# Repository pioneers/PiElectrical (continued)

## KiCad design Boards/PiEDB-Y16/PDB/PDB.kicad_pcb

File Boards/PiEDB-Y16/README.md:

# Power Distribution Board
## Pioneers in Engineering Year 2023-2024
---
Continuation of Y15's PDB.
  
**To Do:**  
- Add battery calibration **(Added switch, WIP for runtime)**
- Create DC-DC Converter **(Work In Progress)**
- Fix battery shorting problem **(Complete)**
- Remove power from data port, optional power using shortings **(Complete)**
- Consider using different port for 5v **(Kept as USB)**

**To Do: Large Revision**
- Find a switch rated for 50A @ 12VDC
- Fuse each motor controller port with 7.5A slow-blow fuse (MC rated for 2x 3.5A motors) (Blows in 20Sec at 10A)
- Add 40A slow-blow fuse for battery. (Blows in 5 min @ 50A, Blows in 20 sec @ 55A) (Battery Max is 55A)
- Add 7.5A slow-blow fuse for 5V rail. (Follows 7.5A max in dc-dc converter)
- Add additional USB plug    
- Rework traces/power planes for large current

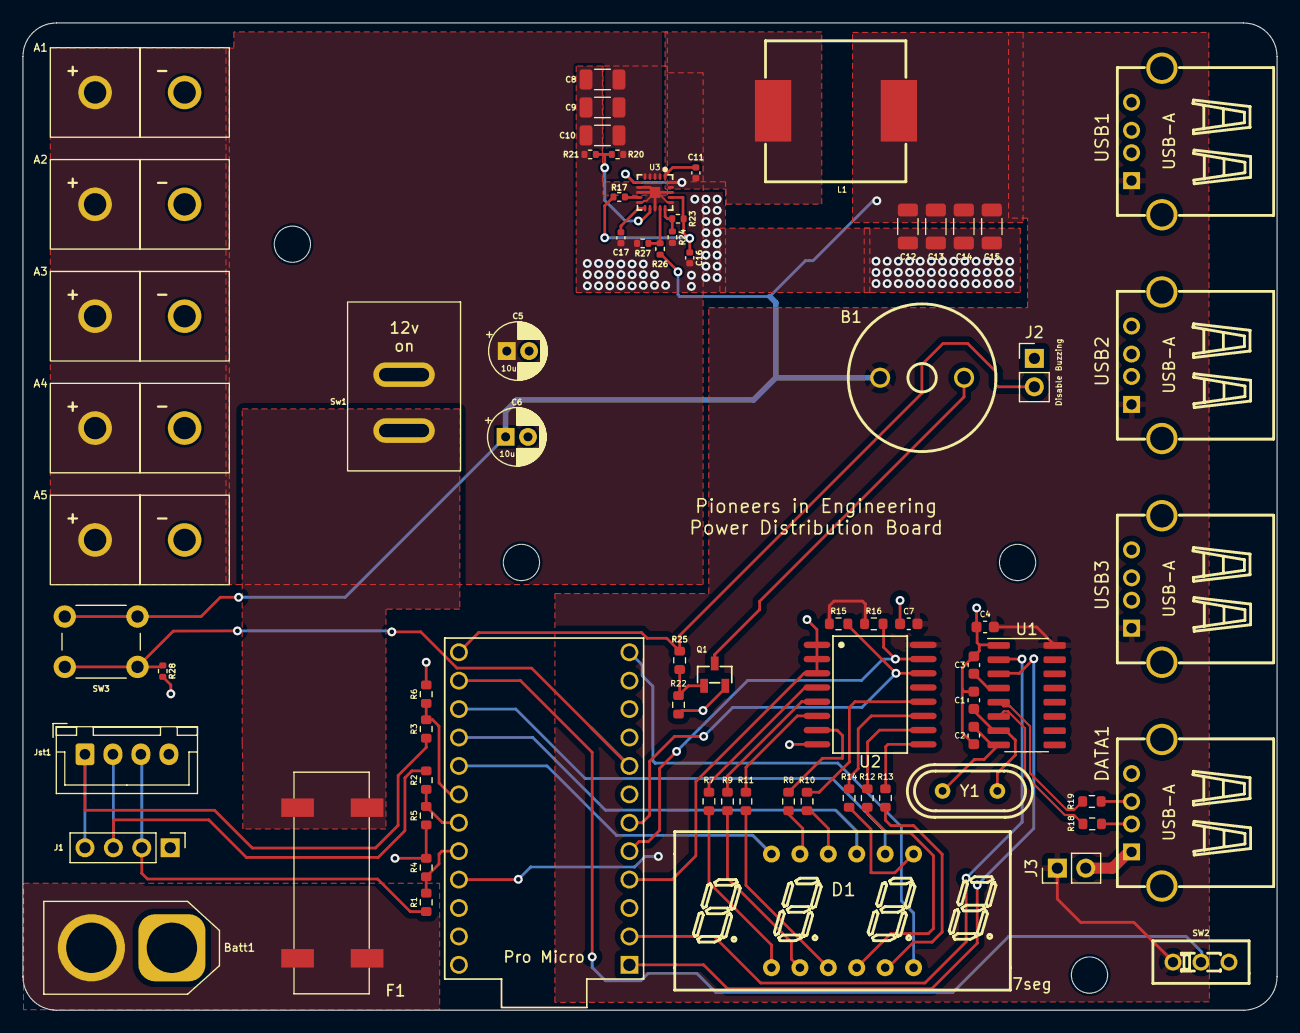
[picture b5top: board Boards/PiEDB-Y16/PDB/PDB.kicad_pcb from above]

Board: 2 copper layers, 112.1 x 88.2 mm, 72 parts (0 on the bottom side), 56 nets.

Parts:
A1, A2, A3, A4, A5: Anderson_Horizontal; anderson_horizontal
B1: Buzzer
Batt1: XT60_F; AMASS_XT60-M_1x02_P7.20mm_Vertical
C1, C2: 22pF; C_0603_1608Metric
C3, C4: 0.1uF; C_0603_1608Metric
C5, C6: 10u; CP_Radial_D5.0mm_P2.00mm
C7: 0.1u; C_0603_1608Metric
C8, C9: 22u; C_1206_3216Metric
C10: 0.1u; C_1206_3216Metric
C11: 0.1u; C_0402_1005Metric
C12, C13, C14, C15: 47u; C_1206_3216Metric
C16, C17: 1u; C_0402_1005Metric
D1: 4_digit_7_segment_display; LED-SEG-TH_12P-L30.0-W13.7-P2.54-S10.16-BL
DATA1: USB; USB-A_female
F1: Fuseholder; Fuse Holder SMD
J1: Conn_01x04; PinHeader_1x04_P2.54mm_Vertical
J2, J3: Conn_01x02; PinHeader_1x02_P2.54mm_Vertical
Jst1: JST-XH_4-pin; JST_XH_B4B-XH-A_1x04_P2.50mm_Vertical
L1: 1.8u; 125CDMCCDS-1R8MC
Pro1: ProMicro; ProMicro-EnforcedTop
Q1: s8050_JSMSEMI; s8050 JSMSEMI
R1, R2, R3: 30000; R_0603_1608Metric
R4, R5, R6: 10000; R_0603_1608Metric
R7, R8, R9, R10, R11, R12, R13, R14: 200; R_0603_1608Metric
R15, R16: 4700; R_0603_1608Metric
R17, R20: 100k; R_0402_1005Metric
R18, R19: 22; R_0603_1608Metric
R21, R27: 15k; R_0402_1005Metric
R22: 2000; R_0603_1608Metric
R23: 200k; R_0402_1005Metric
R24: 33k; R_0402_1005Metric
R25: 100; R_0603_1608Metric
R26: 110k; R_0402_1005Metric
R28: 10k; R_0402_1005Metric
SW2: SW_SPDT; DEALON SS-12D01-G3
SW3: SW_MEC_5E; SW_PUSH_6mm
Sw1: D-SWITCH_MR5-111-C5N-BB; Rocker Switch
U1: CH340G; SOP-16_3.9x9.9mm_P1.27mm
U2: PCF8574; PCF8574T
U3: TPS56C230RJER
USB1, USB2, USB3: USB; USB-A_female
Y1: 12MHz; JYJE S1C12000VWFAC

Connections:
/5v: B1.1 (input), C4.1, C6.1, C7.2, C12.2, C13.2, C14.2, C15.2, J3.1, L1.2, Pro1.21 (VCC), R15.1, R16.1, R26.1, SW2.1 (A), SW3.1, SW3.2, U1.16 (VCC), U2.16 (VDD), USB1.1 (VCC), USB2.1 (VCC), USB3.1 (VCC)
/12v: A1.2 (power), A2.2 (power), A3.2 (power), A4.2 (power), A5.2 (power), C5.1, C8.2, C9.2, C10.2, R20.1, Sw1.2 (Out), U3.2 (VIN), U3.3 (VIN), U3.4 (VIN), U3.5 (VIN)
/A: R8.1, U2.7 (P3)
/B: R14.1, U2.11 (P6)
/BST: C11.2, U3.1 (BST)
/BatCal: Pro1.8 (5), R28.1, SW3.3 (K), SW3.4 (A)
/Buzzer: J2.2, Pro1.13 (10), R25.2
/C: R12.2, U2.10 (P5)
/Cell1: J1.2, Jst1.3 (Pin_1), R1.1
/Cell1+2: J1.3, Jst1.2, R2.1
/Cell1+2+3: J1.4, Jst1.1 (Pin_3), R3.2
/Cell1+2+3_s: Pro1.18 (A1), R3.1, R6.1
/Cell1+2_s: Pro1.19 (A2), R2.2, R5.2
/Cell1_s: Pro1.20 (A3), R1.2, R4.1
/D: R9.2, U2.5 (P1)
/D+: R19.1, U1.5 (UD+)
/D-: R18.1, U1.6 (UD-)
/DP: R11.2, U2.6 (P2)
/Dig1: D1.12 (Dig1), Pro1.17 (A0)
/Dig2: D1.9 (Dig2), Pro1.16 (15)
/Dig3: D1.8 (Dig3), Pro1.15 (14)
/Dig4: D1.6 (Dig4), Pro1.12 (9)
/E: R7.2, U2.4 (P0)
/EN: R20.2, R21.1, U3.12 (EN)
/F: R10.1, U2.12 (P7)
/FB: R26.2, R27.1, U3.14 (FB)
/G: R13.2, U2.9 (P4)
/MODE: R23.2, R24.1, U3.15 (MODE)
/Rx: Pro1.2 (RX), U1.2 (TXD)
/SCL: Pro1.6 (3), R15.2, U2.14 (SCL)
/SDA: Pro1.5 (2), R16.2, U2.15 (SDA)
/SW: C11.1, L1.1, U3.6 (SW), U3.19 (SW), U3.20 (SW)
/Tx: Pro1.1 (TX), U1.3 (RXD)
/VCC: C16.1, R17.1, R23.1, U3.17 (VCC)
/battery: Batt1.2 (power), F1.1 (in1), F1.2 (in2)
/collector: B1.2 (output), Q1.3 (C)
/fuse out: F1.3 (out1), F1.4 (out2), Sw1.1 (In)
/toggle: Pro1.14 (16), SW2.2 (B)
GND: A1.1 (ground), A2.1 (ground), A3.1 (ground), A4.1 (ground), A5.1 (ground), Batt1.1 (ground), C1.2, C2.2, C3.2, C4.2, C5.2, C6.2, C7.1, C8.1, C9.1, C10.1, C12.1, C13.1, C14.1, C15.1, C16.2, C17.2, DATA1.4 (GND), DATA1.5 (Shield), DATA1.6 (Shield), J1.1, J2.1, Pro1.3 (GND), Pro1.4 (GND), Pro1.23 (GND), Q1.2 (E), R4.2, R5.1, R6.2, R21.2, R22.1, R24.2, R27.2, R28.2, SW2.3 (C), U1.1 (GND), U2.1 (A0), U2.2 (A1), U2.3 (A2), U2.8 (VSS), U3.7 (PGND), U3.8 (PGND), U3.10 (NC), U3.13 (AGND), U3.16 (NC), U3.18 (PGND), U3.21 (PGND), USB1.4 (GND), USB1.5 (Shield), USB1.6 (Shield), USB2.4 (GND), USB2.5 (Shield), USB2.6 (Shield), USB3.4 (GND), USB3.5 (Shield), USB3.6 (Shield)
unnamed: D1.11 (A), R8.2
unnamed: D1.7 (B), R14.2
unnamed: D1.4 (C), R12.1
unnamed: D1.2 (D), R9.1
unnamed: D1.3 (DP), R11.1
unnamed: D1.1 (E), R7.1
unnamed: D1.10 (F), R10.2
unnamed: D1.5 (G), R13.1
unnamed: DATA1.3 (D+), R19.2
unnamed: DATA1.2 (D-), R18.2
unnamed: DATA1.1 (VCC), J3.2
unnamed: Q1.1 (B), R22.2, R25.1
unnamed: C3.1, U1.4 (V3)
unnamed: C1.1, U1.7 (XI), Y1.1
unnamed: C2.1, U1.8 (XO), Y1.2
unnamed: R17.2, U3.9 (PGOOD)
unnamed: C17.1, U3.11 (SS)

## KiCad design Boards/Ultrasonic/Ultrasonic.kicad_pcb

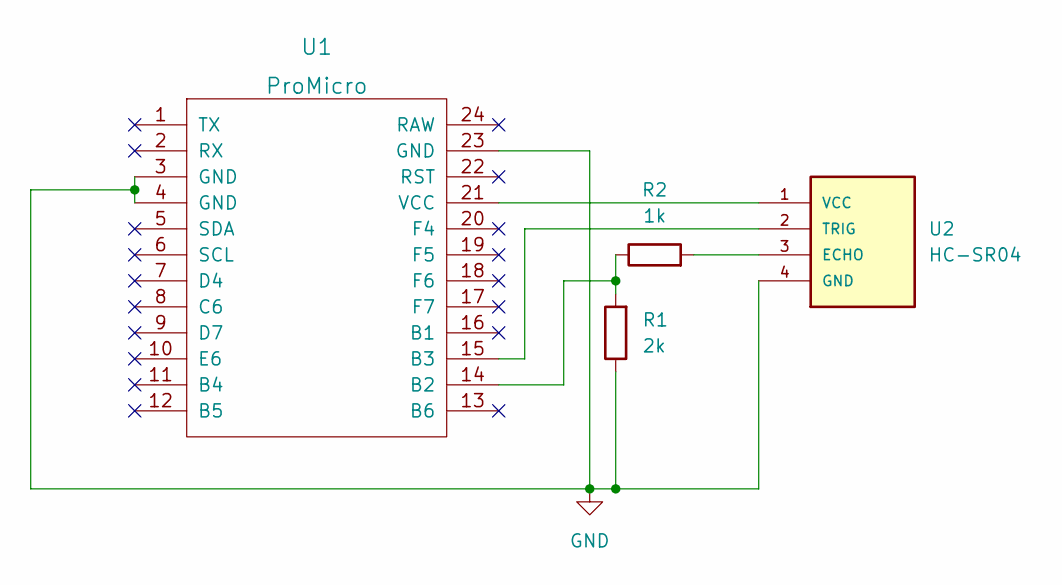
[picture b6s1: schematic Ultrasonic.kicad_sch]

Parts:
R1: 2k; R_0603_1608Metric_Pad0.98x0.95mm_HandSolder
R2: 1k; R_0603_1608Metric_Pad0.98x0.95mm_HandSolder
U1: ProMicro
U2: HC-SR04; XCVR_HC-SR04

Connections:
GND: R1.1, U1.3 (GND), U1.4 (GND), U1.23 (GND), U2.4 (GND)
unnamed: R1.2, R2.1, U1.14 (B2)
unnamed: R2.2, U2.3 (ECHO)
unnamed: U1.15 (B3), U2.2 (TRIG)
unnamed: U1.21 (VCC), U2.1 (VCC)

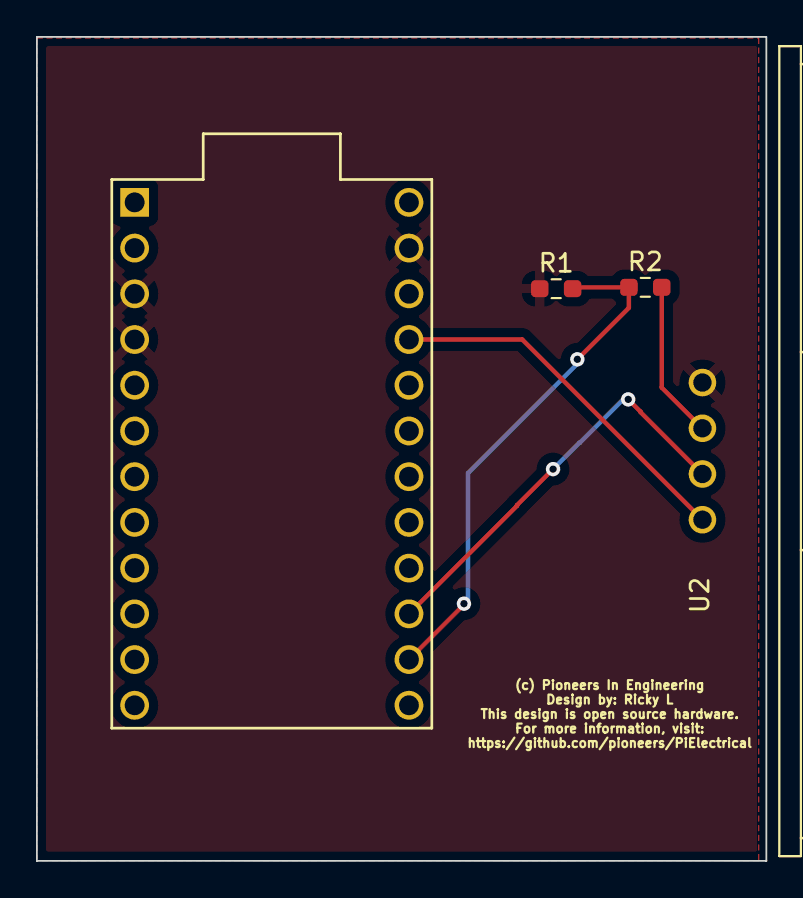
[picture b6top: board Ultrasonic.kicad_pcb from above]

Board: 2 copper layers, 40.5 x 45.8 mm, 4 parts (0 on the bottom side), 5 nets.

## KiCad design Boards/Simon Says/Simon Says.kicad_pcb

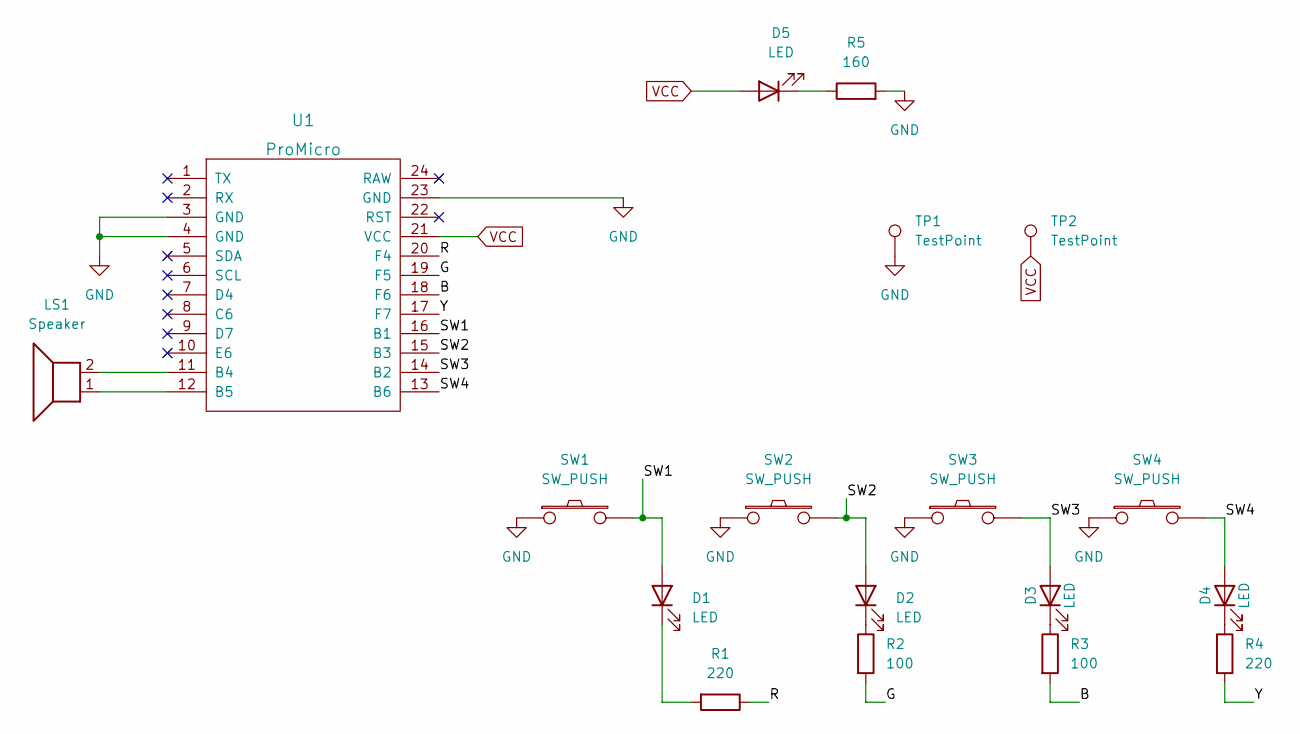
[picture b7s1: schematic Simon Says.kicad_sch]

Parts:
D1, D2, D3, D4, D5: LED; LED_D5.0mm_FlatTop
LS1: Speaker; BUZZER_PS1440P02BT
R1, R4: 220; R_0805_2012Metric_Pad1.20x1.40mm_HandSolder
R2, R3: 100; R_0805_2012Metric_Pad1.20x1.40mm_HandSolder
R5: 160; R_0805_2012Metric_Pad1.20x1.40mm_HandSolder
SW1, SW2, SW3, SW4: SW_PUSH; SW_PUSH_6mm
TP1, TP2: TestPoint; TestPoint_Pad_1.0x1.0mm
U1: ProMicro

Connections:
/B: R3.2, U1.18 (F6)
/G: R2.2, U1.19 (F5)
/R: R1.1, U1.20 (F4)
/SW1: D1.2 (A), SW1.2, U1.16 (B1)
/SW2: D2.2 (A), SW2.2, U1.15 (B3)
/SW3: D3.2 (A), SW3.2, U1.14 (B2)
/SW4: D4.2 (A), SW4.2, U1.13 (B6)
/Y: R4.2, U1.17 (F7)
GND: R5.2, SW1.1, SW2.1, SW3.1, SW4.1, TP1.1, U1.3 (GND), U1.4 (GND), U1.23 (GND)
unnamed: D1.1 (K), R1.2
unnamed: D2.1 (K), R2.1
unnamed: D3.1 (K), R3.1
unnamed: D4.1 (K), R4.1
unnamed: D5.1 (K), R5.1
unnamed: LS1.1, U1.12 (B5)
unnamed: LS1.2, U1.11 (B4)
VCC: D5.2 (A), TP2.1, U1.21 (VCC)

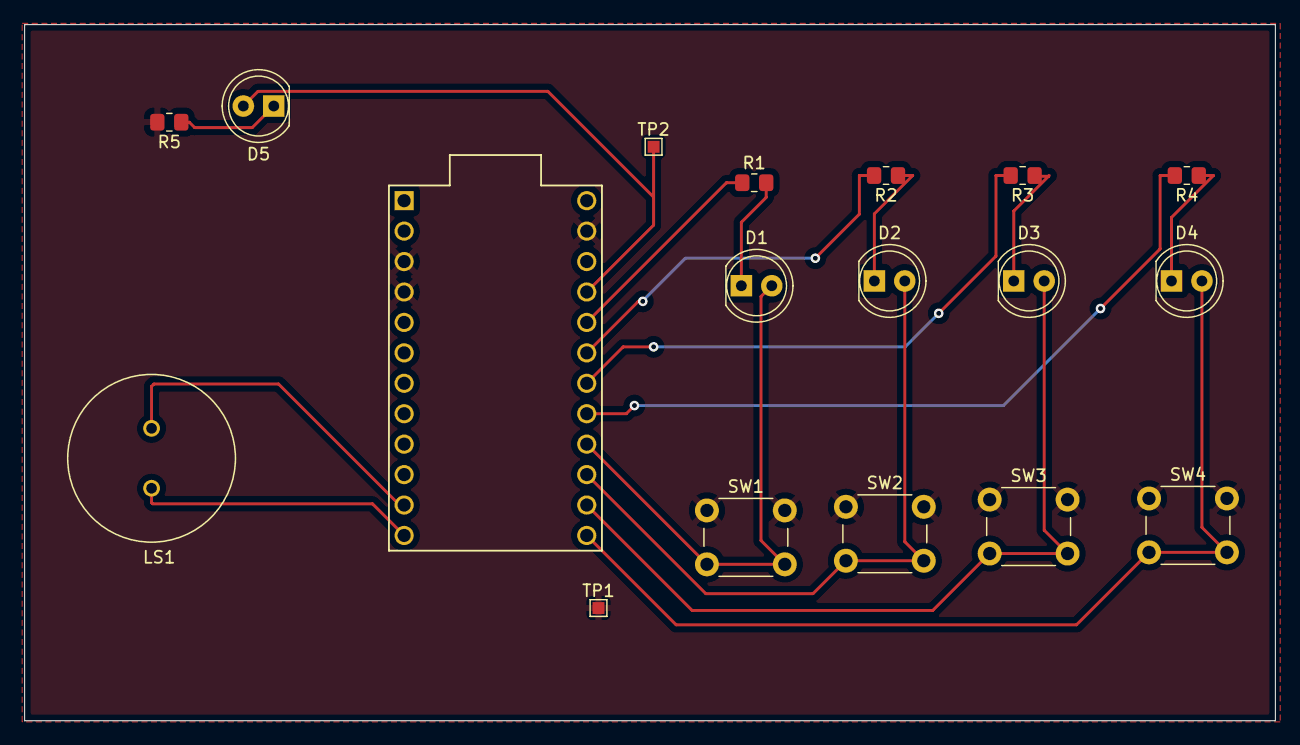
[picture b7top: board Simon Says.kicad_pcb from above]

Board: 2 copper layers, 104.4 x 58.1 mm, 18 parts (0 on the bottom side), 17 nets.

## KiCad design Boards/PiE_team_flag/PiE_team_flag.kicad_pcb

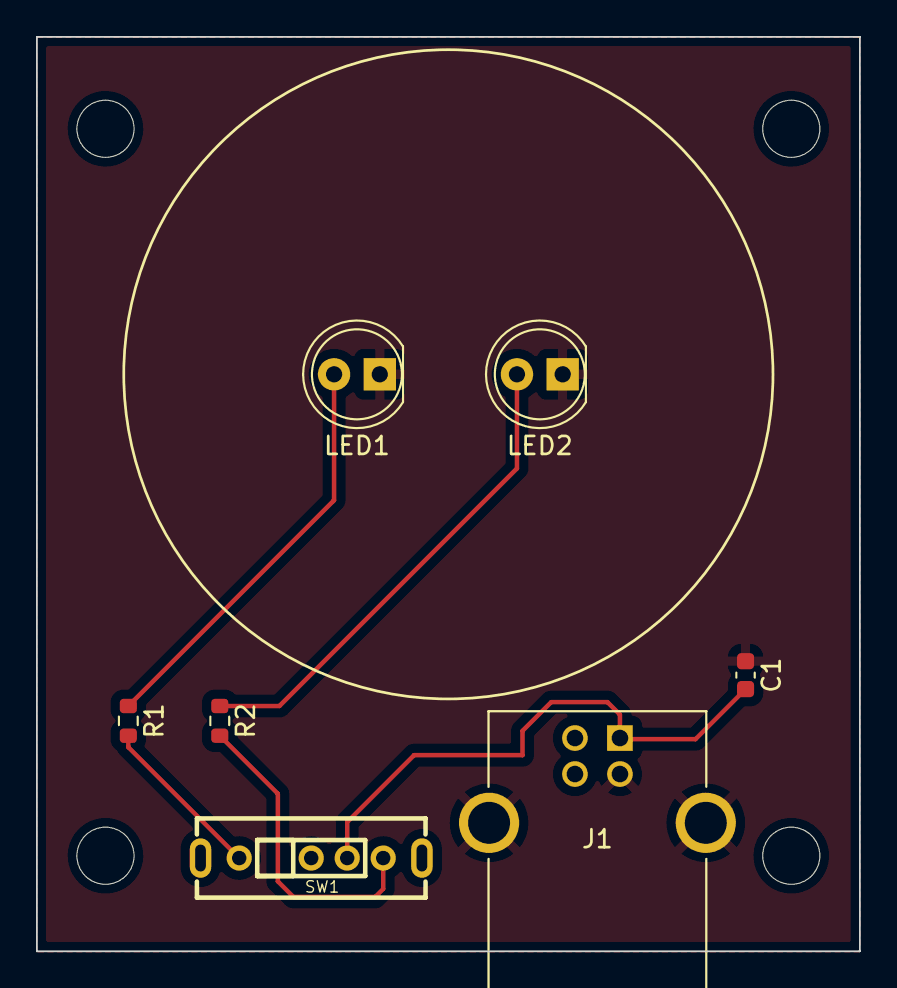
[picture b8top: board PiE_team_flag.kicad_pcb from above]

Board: 2 copper layers, 45.7 x 50.8 mm, 7 parts (0 on the bottom side), 6 nets.

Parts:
C1: .1uF; C_0603_1608Metric
J1: USB_B; OST_USB-B1HSB6
LED1: YEL; LED_D5.0mm
LED2: BLU; LED_D5.0mm
R1: 145; R_0603_1608Metric
R2: 90; R_0603_1608Metric
SW1: SW_SP3T; XKB Connectivity SS13D75L3

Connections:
GND: C1.1, J1.4 (GND), J1.P1, J1.P2, LED1.1 (K), LED2.1 (K)
unnamed: C1.2, J1.1 (VBUS), SW1.3
unnamed: LED1.2 (A), R1.1
unnamed: LED2.2 (A), R2.1
unnamed: R1.2, SW1.1
unnamed: R2.2, SW1.4

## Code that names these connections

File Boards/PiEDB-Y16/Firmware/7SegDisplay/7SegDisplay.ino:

#include <Wire.h>

#define expander B0100000 

#define D1 A0
#define D2 15
#define D3 14
#define D4 9
#define BUZZER 10
#define Cell1 A3
#define Cell2 A2
#define Cell3 A1
#define TOGGLE 16
#include "array.h"
#include "functions.h"

void setup() {     
  Serial.begin(9600);   
  Serial1.begin(9600);        

  pinMode(D1, OUTPUT);  
  pinMode(D2, OUTPUT);  
  pinMode(D3, OUTPUT);  
  pinMode(D4, OUTPUT); 

  pinMode(A3, INPUT);
  pinMode(A2, INPUT);
  pinMode(A1, INPUT);
  
  pinMode(BUZZER, OUTPUT);

  pinMode(TOGGLE, 16);

  pinMode(0, OUTPUT);
  pinMode(1, INPUT);
  
  Wire.begin();

}

char network_switch = -1;
//long previousTime = 0;
// the loop routine runs over and over again forever:
void loop() {
  //unsigned long currentTime = millis();
  analogReference(DEFAULT);
  //float* voltages = parseVoltage(analogRead(Cell1), analogRead(Cell2), analogRead(Cell3));
  float r_v1 = average(Cell1, 50);
  float v_v1 = r_v1 * 20.3/1023.0;
  String o_v1 = DisplayChars(String(v_v1));
  
  float r_v2 = average(Cell2, 50);
  float v_v2 = (r_v2 * 20.1/1023.0) - v_v1;
  String o_v2 = DisplayChars(String(v_v2));
  
  float r_v3 = average(Cell3, 50);
  float v_v3 = (r_v3 * 20.03/1023.0) - v_v2 - v_v1;
  String o_v3 = DisplayChars(String(v_v3));
  
  float r_all = average(Cell3, 50);
  float v_all = r_v3 * 20.03/1023.0;
  String o_all = DisplayChars(String(v_all));

  if (v_all < 11.5 || v_v1 < 3.8 || v_v2 < 3.8 || v_v3 < 3.8) {
  tone(10, 800);
  } else if (v_all > 12 && v_v1 > 4.0 && v_v2 > 4.0 && v_v3 > 4.0) {
    noTone(BUZZER);
  }
  
  Serial.println(digitalRead(TOGGLE));
  
  displayString("CEL1", 2000);
  displayString(o_v1, 2000);
  displayString("CEL2", 2000);
  displayString(o_v2, 2000);
  displayString("CEL3", 2000);
  displayString(o_v3, 2000);
  displayString("ALL ", 2000);
  displayString(o_all, 2000);

}

void displayString(String phrase, int length) {
  for (int i = 0; i < length/8; i++) {
    if (digitalRead(TOGGLE) != network_switch) {
      network_switch = digitalRead(TOGGLE);
      Serial1.println(digitalRead(TOGGLE));
    }
    printDigit(phrase[0], D1);
    delay(2);
    printDigit(phrase[1], D2);
    delay(2);
    printDigit(phrase[2], D3);
    delay(2);
    printDigit(phrase[3], D4);
    delay(2);
  }
}


/* gets the average values from an analog pin.
   Returns the averaged value of the pin. */
float average(int pin, int samples) {
  float sum = 0.0;
  for (int i = 0; i < samples; i++) {
    sum += analogRead(pin);
  }
  float average = sum / samples;
  return average;
}

void expanderWrite(byte _data) {
  Wire.beginTransmission(expander);
  Wire.write(_data);
  Wire.endTransmission(); 
}

void reset() { 
  digitalWrite(D1, LOW);
  digitalWrite(D2, LOW);
  digitalWrite(D3, LOW);
  digitalWrite(D4, LOW);
  expanderWrite(0b11111111);
  //for(byte i = 0 ; i < 8 ; i++){
    //digitalWrite(seg[i], HIGH); //mode = 1; for each segment, 1 = off and 0 = on
  //}
}

int printDigit(char Chara, int digitPort) { 
  reset(); 
  int character = -1;
  digitalWrite(digitPort, HIGH);
  for(int i = 0 ; i < charsInArray ; i++) {
    if (Chara == Char[i][1]) { //set character equal to the corresponding array index
     character = i;
    }
  }
  expanderWrite(~Char[character][0]);
  
}

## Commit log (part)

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2017-01-03 Update ATX conn and 5v Buck
2017-01-03 Update the ATX part and move around to fit board
2017-01-03 Renew the pdb gerb
2017-01-04 Update molex part
2017-01-05 Update molex to have name
2017-01-05 Update molex, remove old labels;
2017-01-06 Add silkscreen for andersons and molex
2017-01-06 Update revision and cam
2017-01-06 Add the production gerber
2017-01-07 Update PDB and Servo in PRD Gerb
2017-01-07 HOPEFULLY FINAL PROD GERB
2017-01-14 Migrate over Dougs docu-packet stuff
2017-01-14 Remove yaml and caption
2017-01-14 Add docu info
2017-01-17 Added top stencil to docu packet
2017-01-17 Fix scaling on laser stencil
2017-01-26 Improving README to reflect documentation changes
2017-01-28 adds status_lights_driver.py as modified from forseti2 to control field lights
2017-02-01 Fix drill hole sizes for 2,3,4 pin screw headers.
    If you're using these parts on your board, you'll need to update the library "Library -> Update All" to use this new part
2017-02-02 Controlling all lights from command line
2017-02-02 Add docu packets
2017-02-02 Add docu generating script
2017-02-03 Dank message
2017-02-03 Removed backups
2017-02-03 Made it better
2017-02-04 Added indexes to buttons which correspond to their master field light.
2017-02-04 bye bye main
2017-02-04 added the forbidden function
2017-02-04 Integrating lights with buttons!
2017-02-04 fixed formatting errors for Averal.
2017-02-04 UNLIMITED POWER
2017-02-04 Added buzzer support
2017-02-04 Finished product (disco still doesnt' work though. Or buzzers)
2017-02-04 Add FC RFID code
2017-02-08 I made the disco button actually functional.
2017-02-16 Add pullup resistors to encoders
2017-02-16 Adding Relay part
2017-02-18 Made it so it won't crash when you load images.
2017-02-18 Remove old status lights driver
2017-02-22 Add script info to README for docu packet generation
2017-02-23 Adding images for SmartSensor Wiki
2017-02-23 Adding images for SmartSensor Wiki (#68)
2017-02-23 More images
2017-02-23 Averal/wiki (#69)
    * Adding images for SmartSensor Wiki
    * More images
2017-03-09 pic for TeamFlag
2017-03-09 Averal/wiki (#72)
    * Adding images for SmartSensor Wiki
    * More images
    * pic for TeamFlag
2017-05-27 Reorganize and rename
2017-05-27 Update to use different directory
2017-05-27 Add Y9 Folder for archiving purposes
2017-05-27 Fix markdown
2017-05-27 Update Makefile
2017-05-27 Add PDB readme
2017-05-27 Add more documentation
2017-05-27 Add more todo and organize
2017-05-27 Reorganize archive
2017-05-27 Add my comments on all boards
2017-05-27 Add aravinds wisdom
2017-05-31 Move around images to one location
2017-05-31 Add eagle directories picture
2017-06-01 Update README.md
    beep boop
2017-06-01 Added Micro USB
2017-06-01 Added SPDT switch to lib
2017-06-01 Team flag schematic/board WIP
2017-06-02 Replaced SPDT with SP3T slide switch, and fixed teamflag v2
2017-06-02 Fixed some issues with SP3T switch and board layout
2017-06-07 Fixed clearence issues with the SP3T slide
2017-06-07 Merged libraries
2017-06-07 Fixed board with new part updates
2017-06-07 Appeasing the master
2017-06-07 swag eata that averal
2017-06-10 Added comments to boards
    and also fixed grammer mistakes.
2017-06-11 Added comments to boards (#78)
    Thanks Doug
2017-07-02 I don't know
2017-07-02 Added the MUX and the OP amp. also imported the DIP 8 and 16 pin packages
2017-07-02 Deleted old team flag from main folder. It still exists in Y9 folder
2017-07-08 Fix the routing issues
2017-07-31 Change pullup resistor vcalue
2017-07-31 Add gain for antenna
2017-08-19 team flag fixed <3 margo
2017-08-19 fixed a thing in team flag
2017-08-26 PMW in motor controller to PWM
2017-08-31 ayy lmao
2017-08-31 REEEEEEEEEEEEEEEEEEEEEEEEEEEEEEEEEEEEEEEEEEEEEEEEE ADDED SOT23-6pin REEEEEEEEEEEEEEEEEEEEEEEEEEEEEEEEEEE
2017-09-01 ggetting caught up
2017-09-01 SO MUCH
2017-09-01 Forgot to power the op amp
2017-09-07 Started routing
2017-09-07 Semi done routing
2017-09-07 Finished
2017-09-07 Got rid of warning error when opening library
2017-09-07 Fixed a 90 deg angle
2017-09-09 add test file and documentation for line break sensor
2017-09-09 Readd the piecam
2017-09-16 Add testing procedure
2017-09-21 Labeled Servos correctly and changed rev cycle
2017-09-21 Updated Rev on frames (does not necessarily mean that everything is good-to-go)
2017-09-21 Rerouted EN to A3 from 14
2017-09-23 cronCH
2017-09-23 rev a is a gogo
2017-10-05 Create TeamFlag
2017-10-07 made hole guys smaller for usb and labeled positive one
2017-10-14 margo moved the arduino slightly to the left so it doesn't touch the hole guy
2017-10-14 Added test code for test board
2017-10-14 more ocd alignment changes
2017-10-14 fixed the actual thing seiya wanted -- moved the arduino(?) to the middle between the pillar/hole things
2017-10-14 actually actually fixed the thing seiya wanted -- the arduino is centered and the rfid is correctly moved -- also hopefully the drill hole matches up with the other thing (top right corner)
2017-10-15 rev 10b done, dfm all good2go
2017-10-15 REV B PLEASE WORK
2017-10-19 changed pull-ups to 10k my d00d
2017-10-28 Added back 5V buck and added caps. DRC clean
2017-11-02 Please, PDB, please work. Also I updated ATX connector.
2017-11-09 vital important work changing rev to prod i am a very significant part of this team -- team flag
2017-11-09 Updated revision names
2017-11-09 Updated Revision Name
2017-11-09 I hate my life
2017-11-30 Created Distance Sensor
2018-01-27 Board up
2018-01-27 Finish solar scramble
2018-01-28 Make some changes
2018-01-29 Finish up board
2018-02-10 add pulldown labels
2018-06-30 Added resistor array
2018-07-04 Modified resistor array part
2018-07-07 Created new 5PIN part to replace screw terminal
2018-07-07 add solder jumper part
2018-07-08 Created rough version of sensor board, split from TwistIt
2018-07-10 Revised SensorBoard and fixed TwistIt
2018-07-15 Split motor controller from TwistIt and modified resistor array to account for size errors
2018-07-21 Modified motor controller board
2018-07-21 add mc chip
2018-07-21 Created new radial electrolytic capacitor
2018-07-26 Completed rough version of motor controller chip board
2018-07-26 Finished prototype board
2018-07-26 Fixed font style for some text
2018-07-27 Centered board and added board name
2018-09-02 Added mc chip to motor controller board
2018-09-06 made directory for PDB battery management project
2018-09-06 Finished prototype of motor controller board
2018-09-06 Fixed LED color values not showing up
2018-09-29 Modifying motor controller
2018-09-29 Rev B Motor Controller
2018-10-07 added protoboard files and code for testing
2018-10-13 completed code for BQ76920 library and wrote tests
2018-10-21 made protoboard 2 for BQ76920
2018-10-27 Fixed routing to arduino pins
2018-10-27 Fixing sizes
2018-10-27 Created gerbs
2018-11-03 added final rev2 protoboard for BQ76920
2018-12-06 Modified tcream layer for reflowing
2018-12-10 PDB tcream for reflowing
2019-03-16 Miscellaneous
2019-04-13 shift register
2019-04-20 add a better mc33926 footprint and schematic
2019-04-25 started board
2019-04-27 board
2019-04-27 finished board routing ish
2019-06-23 start 6-motor controller project
2019-06-27 make and organize schematic for MCDB
2019-07-10 added atmega328pb-au to lib
2019-07-11 no more ignore pie.lbr
2019-07-11 ending...
2019-07-11 hopefully didn't break pie.lbr
2019-07-11 Started process of using new MC symbol
2019-07-11 yeet that lib
2019-07-13 Modified MC33926 part
2019-07-13 Started modifying motor controller board
2019-07-14 pdb layout and added parts to library
2019-07-14 finished rev1 pdb:
2019-07-14 yeet
2019-07-18 Added new MC part for the third time
2019-07-18 edited to accomodate new symbol
2019-07-18 add 32U4 to mcdb schematic
2019-07-20 Added atmega32u4 to library
2019-07-20 added new crystal footprint
2019-07-20 continued work on MCDB
2019-07-25 connected remaining pins on 32U4, added USB B and USB Micro
2019-07-25 added many capacitors (to USB D lines, to digital logic VCC for each MC, and three to VPWR)
2019-07-29 starting pdb rev2
2019-08-01 start working on animatronic
2019-08-01 sherwin's stupid fun adventure
2019-08-08 Continued layout of MCDB
2019-08-15 goddamn u sherwin; also deleted one unnecessary polygon
2019-08-15 tried routing some signals from MCU
2019-08-23 finished PDB, motorcontroller test board, and updates to pie lib
2019-08-24 Slight modification
2019-09-26 just pdb things
2019-11-02 Working on new motor controller
2019-11-02 Fixing conflicts
2019-11-02 Continued working on new motor controller
2019-11-03 Continuing work
2019-11-03 fixerd
2019-11-03 Rev A
2019-11-05 thweou th
2019-11-05 isp pls
2019-11-05 Routed the ISP Connector
2019-11-05 things
2019-11-07 added example
2019-11-14 Print cell voltages and time
2019-11-16 ultrasonic_ir board
2019-11-16 Gerb file for motor controller v2
2019-11-16 Fixing merge conflicts
2019-11-16 Fixing more errors in library
2019-11-17 fixed silkscreen fonts and ground pins
2019-11-26 usir files
2019-11-27 Rev B of the TI motor controller
2019-11-28 trerewrewr
2019-12-05 lets goo
2019-12-05 Removed code relating to bmic
2019-12-05 team flag screw terminal
2019-12-05 yeey
2019-12-05 fixed lib
2019-12-21 Modified encoder labelling
2019-12-27 Added heartbeat, rx leds
2019-12-27 Slightly modified motor controller
2019-12-27 Generated gerbers for production
2019-12-27 gerbs
2019-12-27 fixed pdb drc
2020-02-13 Added color sensor symbol
2020-02-15 Printout for PDB
2020-02-16 added arduino bootloadr flashing package
2020-02-20 Color sensor day 2
2020-02-20 color sensor cam job
2020-02-22 Color sensor gerb
2020-06-27 Added new motor controller
2020-06-27 ultrasonic
2020-06-27 add drv8872 library
2020-08-29 did the pcb stuff for the distancce sensor
2020-09-03 it all works now finally, (ultrasonic ir boards)
2020-11-28 please no mere conflict
2020-12-27 line follower schematic
2021-01-21 added mux to line follower
2021-01-30 lf updates
2021-01-30 adding 1st2020mc brd/sch
2021-02-04 more updates
2021-02-06 line follower done, code added
2021-02-07 2020mc v2
2021-02-13 catching up
2021-02-13 fixmylife
2021-02-13 maybe fixed
2021-02-18 2/17 mc2020 update
2022-03-31 Create Test
2022-03-31 Create blah
2022-03-31 Update blah
2023-08-26 adding PiEDB Y15 files
2023-08-29 testing image height
2023-08-29 added setup image for testing
2023-08-29 testing images again with correct filenames
2023-08-29 one last time... picture should work
2023-08-29 testing expandable sections
2023-08-29 added insructions to setup KiCad and symbol library
2023-08-29 Moved old eagle src files into hidden directory
2023-08-29 Moved some fabrication files and libraries
2023-08-29 trying larger collapsible sectoin
2023-08-29 trying again
2023-08-29 and again
2023-08-29 nah collapsible looks bad on large sections
2023-10-05 Re-organized folders and files
2023-10-05 updated structure section
2023-10-06 Committing Y15 PDB
2023-10-06 added kicad backup files to gitignore
2023-10-06 fix images
2023-10-20 Add images to tutorial
2023-10-21 update PDB to new version of kicad
2024-01-21 modified gitignore
2024-01-21 put new PDB in boards
2024-01-21 roughly finished layout for new dc-dc converter
2024-01-21 add new footprints TPS56C230RJER
2024-01-27 added mc chip footprint and symbol
2024-01-27 servo contoller
2024-01-29 updated BOM
2024-02-01 finished servo layout
2024-02-02 Ordered Servo Controller
2024-02-03 Worked on PDB Revision
2024-02-06 pictures of layout
2024-02-24 Revision of PDB
2024-03-10 Make new test board
2024-03-11 Added to do for PDB
2024-03-11 added 3d model for promicro
2024-03-16 made new PDB prototype
2024-03-16 added to-do
2024-04-11 Starting Revamp of MC
2024-04-25 atmega328p_prototype
2024-04-26 Created TTL Converter
2024-04-26 Put TTL Converter in correct folder
2024-06-07 PDB Updates
2024-06-07 added simon says and ultrasonic
2024-09-14 updated library: (BS-7) battery, TLC555 (timer)
2024-09-14 added Y16_motorControllerConversion project files
2024-09-14 starting onboarding
2024-09-14 updated TurboPDB schematic
2024-09-21 updated TurboPCB schematic and footprint; incomplete connector socket footprint assignment
2024-10-12 added 1mm through-hole pad to PiE footprint library for onboarding. Finished onboarding footprint.
2024-10-12 added turbo dxf files for onboarding footprint
2024-11-21 Added TCS230
2025-01-30 created PDB files from KiCad
